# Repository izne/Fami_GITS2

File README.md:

# Fami_GITS2
GITS2 board for Famicom. Generates test patterns for the screen.

## Based on GITS2 project
[GITS2 Project](https://qrx.narod.ru/izm/g_its.htm)

[GITS2 ROMs](https://ftp.radio.ru/pub/2002/10/gits2/)

# Schematic
Schematic based on original drawing. ERC is OK.

# Board renders
The PCB is work in progress, here a current render of the front side:

## Famicom cartridge
Using HVC-TGROM-01

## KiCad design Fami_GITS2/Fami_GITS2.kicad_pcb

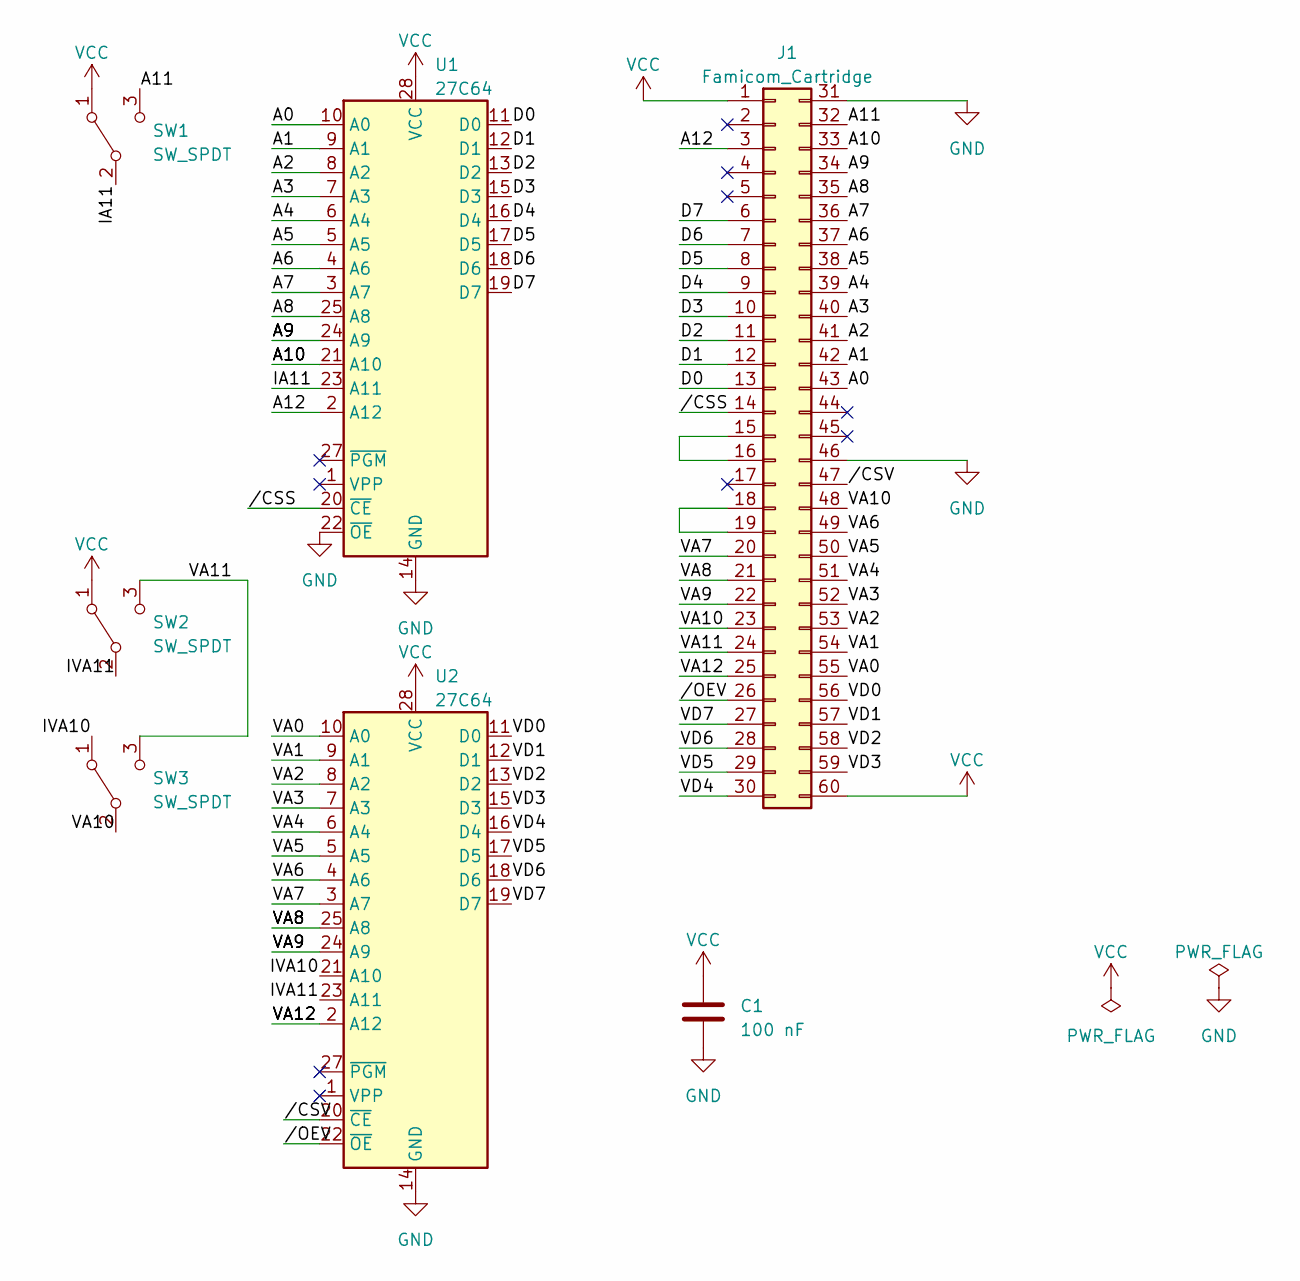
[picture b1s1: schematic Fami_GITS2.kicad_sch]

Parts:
C1: 100 nF; C_Disc_D3.0mm_W1.6mm_P2.50mm
J1: Famicom_Cartridge; HVC-TGROM-01
SW1, SW2, SW3: SW_SPDT; SW_SPDT_CK-JS102011SAQN
U1, U2: 27C64; DIP-28_W15.24mm

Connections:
/A0: J1.43, U1.10 (A0)
/A1: J1.42, U1.9 (A1)
/A2: J1.41, U1.8 (A2)
/A3: J1.40, U1.7 (A3)
/A4: J1.39, U1.6 (A4)
/A5: J1.38, U1.5 (A5)
/A6: J1.37, U1.4 (A6)
/A7: J1.36, U1.3 (A7)
/A8: J1.35, U1.25 (A8)
/A9: J1.34, U1.24 (A9)
/A10: J1.33, U1.21 (A10)
/A11: J1.32, SW1.3 (C)
/A12: J1.3, U1.2 (A12)
/D0: J1.13, U1.11 (D0)
/D1: J1.12, U1.12 (D1)
/D2: J1.11, U1.13 (D2)
/D3: J1.10, U1.15 (D3)
/D4: J1.9, U1.16 (D4)
/D5: J1.8, U1.17 (D5)
/D6: J1.7, U1.18 (D6)
/D7: J1.6, U1.19 (D7)
/IA11: SW1.2 (B), U1.23 (A11)
/IVA10: SW3.1 (A), U2.21 (A10)
/IVA11: SW2.2 (B), U2.23 (A11)
/VA0: J1.55, U2.10 (A0)
/VA1: J1.54, U2.9 (A1)
/VA2: J1.53, U2.8 (A2)
/VA3: J1.52, U2.7 (A3)
/VA4: J1.51, U2.6 (A4)
/VA5: J1.50, U2.5 (A5)
/VA6: J1.49, U2.4 (A6)
/VA7: J1.20, U2.3 (A7)
/VA8: J1.21, U2.25 (A8)
/VA9: J1.22, U2.24 (A9)
/VA10: J1.23, J1.48, SW3.2 (B)
/VA11: J1.24, SW2.3 (C), SW3.3 (C)
/VA12: J1.25, U2.2 (A12)
/VD0: J1.56, U2.11 (D0)
/VD1: J1.57, U2.12 (D1)
/VD2: J1.58, U2.13 (D2)
/VD3: J1.59, U2.15 (D3)
/VD4: J1.30, U2.16 (D4)
/VD5: J1.29, U2.17 (D5)
/VD6: J1.28, U2.18 (D6)
/VD7: J1.27, U2.19 (D7)
//CSS: J1.14, U1.20 (~CE)
//CSV: J1.47, U2.20 (~CE)
//OEV: J1.26, U2.22 (~OE)
GND: C1.1, J1.31, J1.46, U1.14 (GND), U1.22 (~OE), U2.14 (GND)
unnamed: J1.15, J1.16
unnamed: J1.18, J1.19
VCC: C1.2, J1.1, J1.60, SW1.1 (A), SW2.1 (A), U1.28 (VCC), U2.28 (VCC)

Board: 2 copper layers, 7 parts (0 on the bottom side), 52 nets, no tracks yet.

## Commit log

2024-02-13 Work in progress of the board
2024-02-13 Doc one
2024-03-29 Completed schematic. PCB complete without routing.
2024-03-29 Typos
